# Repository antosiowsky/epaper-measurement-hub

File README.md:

# Epaper-EnvMonitor

A low-power environmental monitoring hub with an e-paper display, based on the M5StampS3 processor. It features a BME688 sensor for temperature, humidity, and air quality measurement, along with data storage and wireless communication.

## Features
- **Real-time environmental monitoring** (temperature, humidity, air quality)
- **E-paper display** for low-power data visualization
- **Data storage** for historical measurements
- **Wireless communication** (Wi-Fi/Bluetooth) for remote access
- **Energy-efficient design** suitable for battery-powered operation

## Hardware Components
- **M5StampS3** – ESP32-S3 based microcontroller
- **BME688** – Temperature, humidity, and gas sensor
- **E-paper display** – Low-power screen for data visualization
- **Memory module** – For data logging and storage

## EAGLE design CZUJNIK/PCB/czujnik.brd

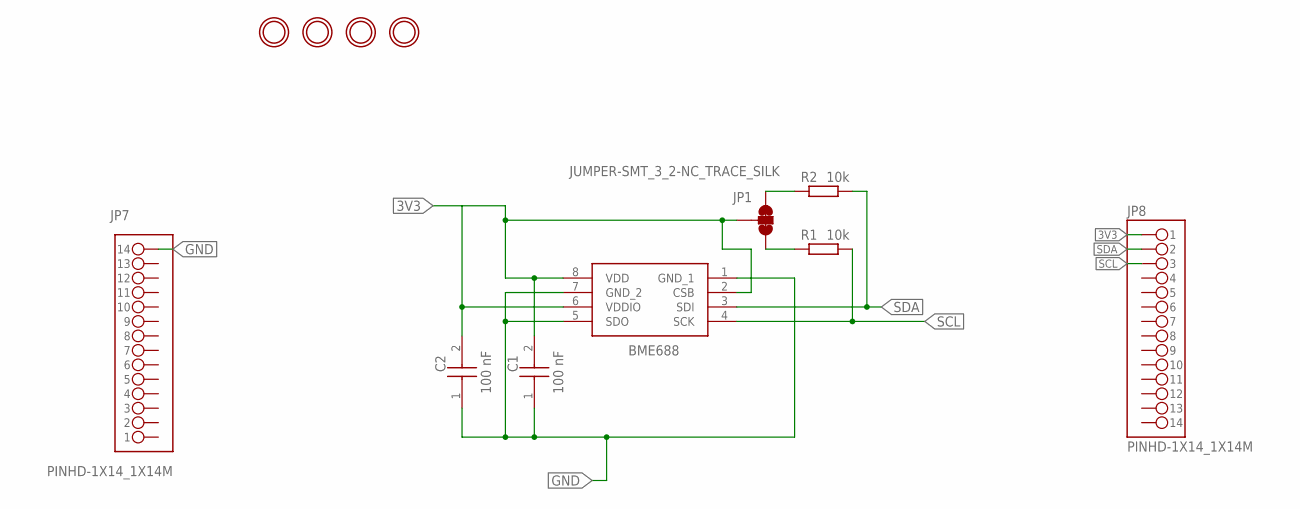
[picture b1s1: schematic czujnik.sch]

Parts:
BME688: BME688
C1, C2: C0603X104K1RACTU; CAPC1608X100N
JP1: JUMPER-SMT_3_2-NC_TRACE_SILK; SMT-JUMPER_3_2-NC_TRACE_SILK
JP7, JP8: PINHD-1X14_1X14M; 1X14
R1, R2: 10k; RESC1005X40
U$2, U$3, U$4, U$6: MOUNTINGHOLE2.5; MOUNTINGHOLE_2.5_PLATED

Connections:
3V3: BME688.2 (CSB), BME688.6 (VDDIO), BME688.8 (VDD), C1.2, C2.2, JP1.2, JP8.1
GND: BME688.1 (GND_1), BME688.5 (SDO), BME688.7 (GND_2), C1.1, C2.1, JP7.14
unnamed: JP1.1, R2.1
unnamed: JP1.3, R1.1
SCL: BME688.4 (SCK), JP8.3, R1.2
SDA: BME688.3 (SDI), JP8.2, R2.2

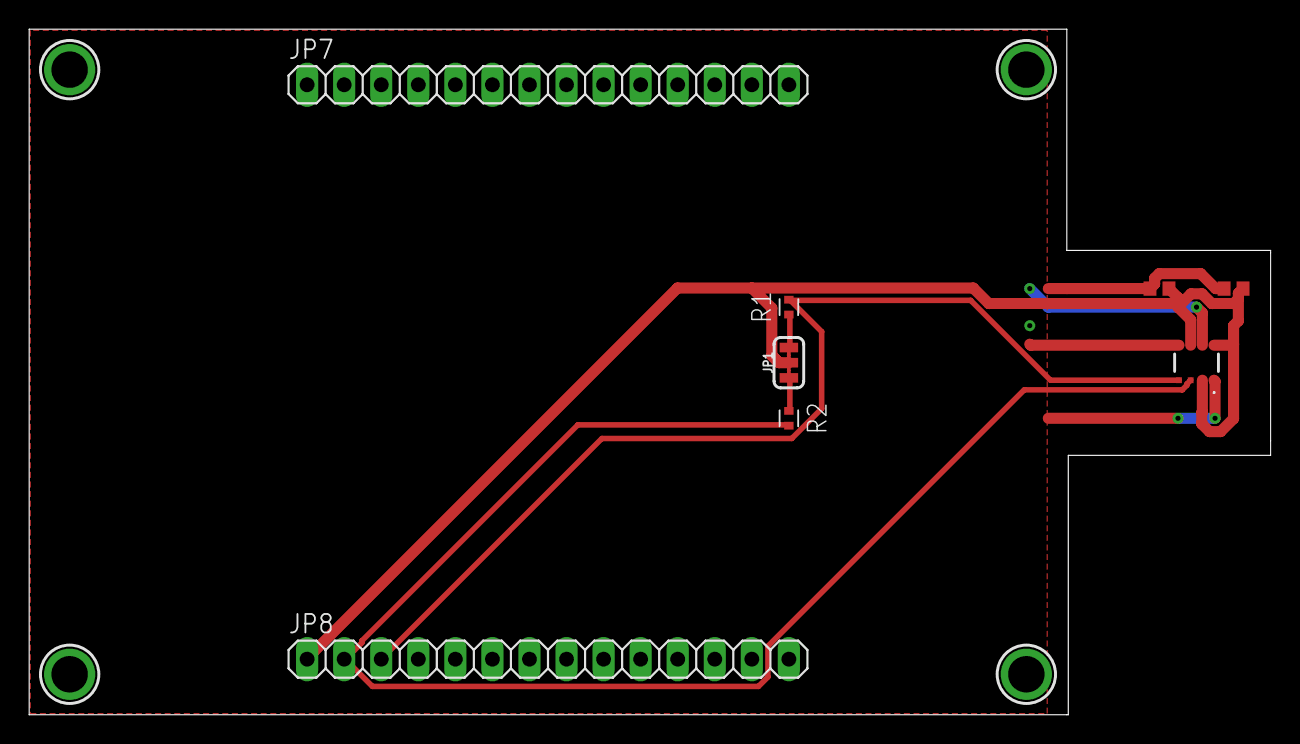
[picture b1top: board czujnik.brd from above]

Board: 2 copper layers, 85.1 x 47.0 mm, 12 parts (0 on the bottom side), 6 nets.

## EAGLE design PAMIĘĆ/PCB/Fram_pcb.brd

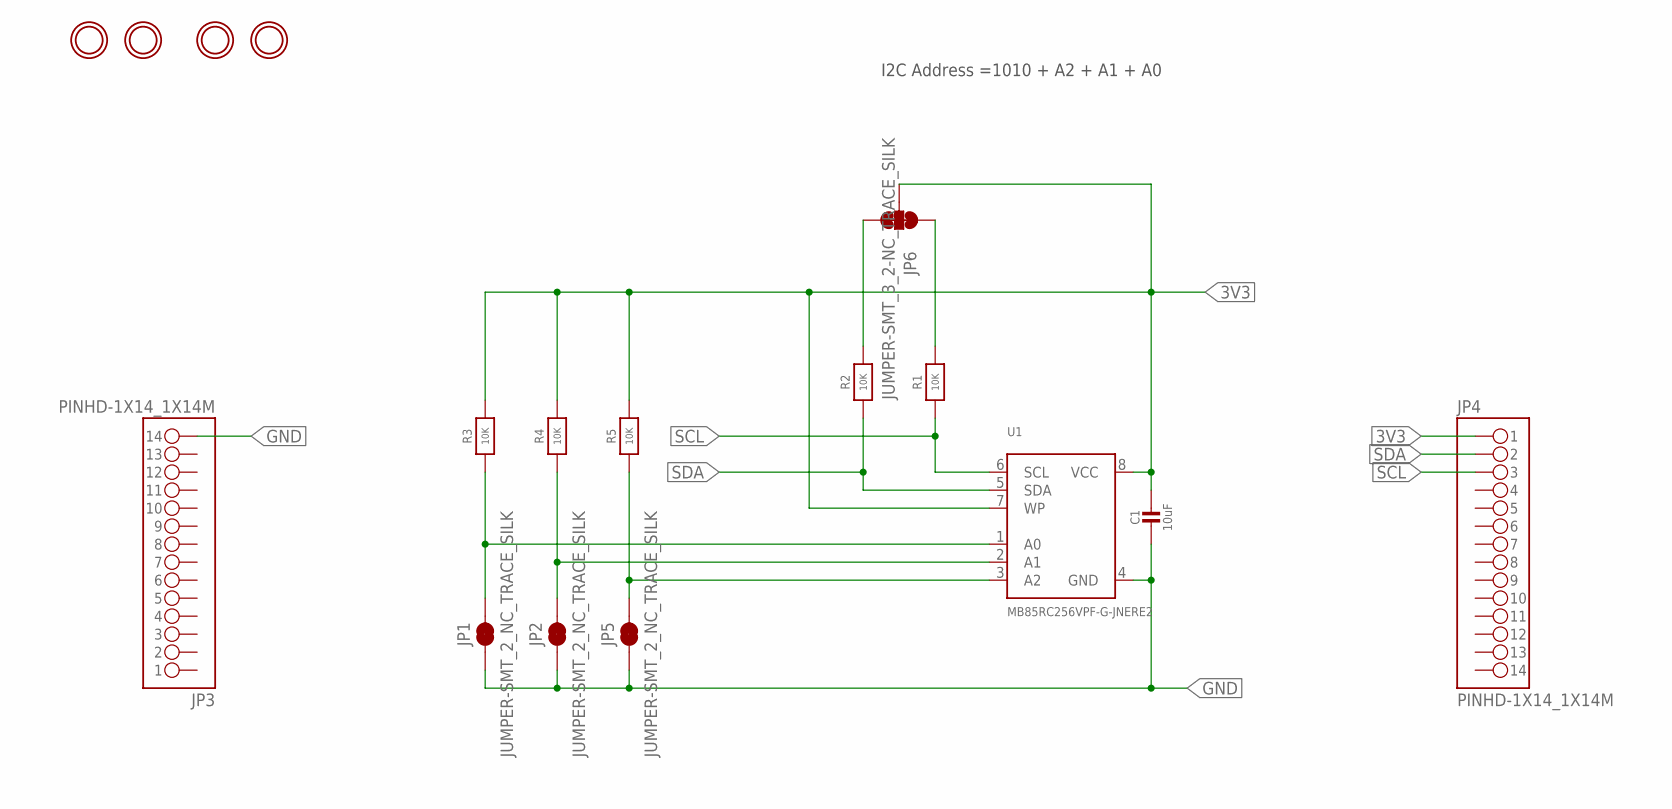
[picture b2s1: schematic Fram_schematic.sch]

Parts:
C1: 10uF; _0805MP
JP1, JP2, JP5: JUMPER-SMT_2_NC_TRACE_SILK; SMT-JUMPER_2_NC_TRACE_SILK
JP3, JP4: PINHD-1X14_1X14M; 1X14
JP6: JUMPER-SMT_3_2-NC_TRACE_SILK; SMT-JUMPER_3_2-NC_TRACE_SILK
R1, R2, R3, R4, R5: 10K; _0805MP
U1: MB85RC256VPF-G-JNERE2; SOIC8_208MIL
U$2, U$3, U$5, U$6: MOUNTINGHOLE2.5; MOUNTINGHOLE_2.5_PLATED

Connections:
3V3: C1.1, JP4.1, JP6.2, R3.2, R4.2, R5.2, U1.7 (WP), U1.8 (VCC)
GND: C1.2, JP1.1, JP2.1, JP3.14, JP5.1, U1.4 (GND)
SCL: JP4.3, JP6.1, R1.1, R1.2, U1.6 (SCL)
SDA: JP4.2, JP6.3, R2.1, R2.2, U1.5 (SDA)
SDA1: JP1.2, R3.1, U1.1 (A0)
SDA2: JP2.2, R4.1, U1.2 (A1)
SDA3: JP5.2, R5.1, U1.3 (A2)

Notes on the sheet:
I2C Address =1010 + A2 + A1 + A0

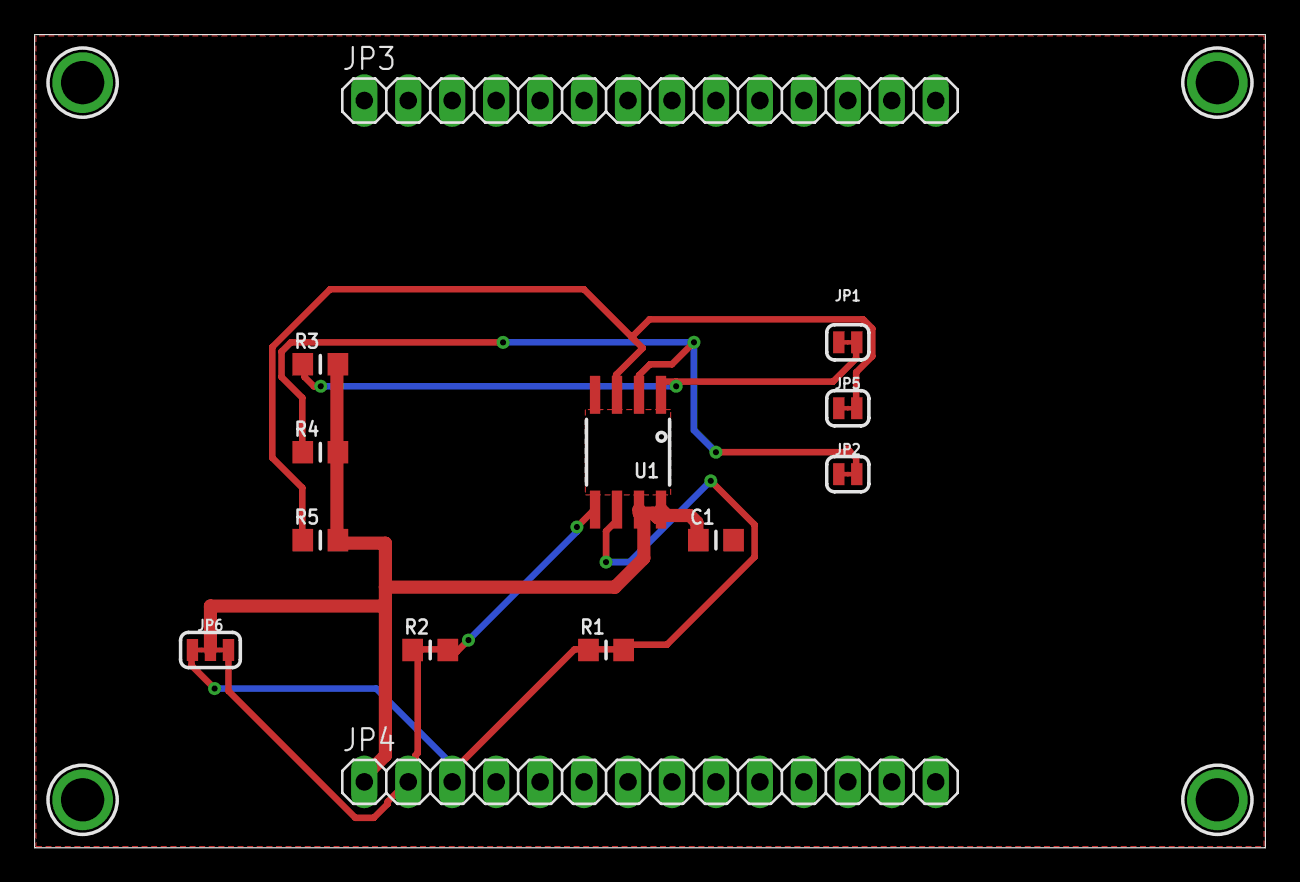
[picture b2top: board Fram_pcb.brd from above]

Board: 2 copper layers, 71.1 x 47.0 mm, 17 parts (0 on the bottom side), 7 nets.

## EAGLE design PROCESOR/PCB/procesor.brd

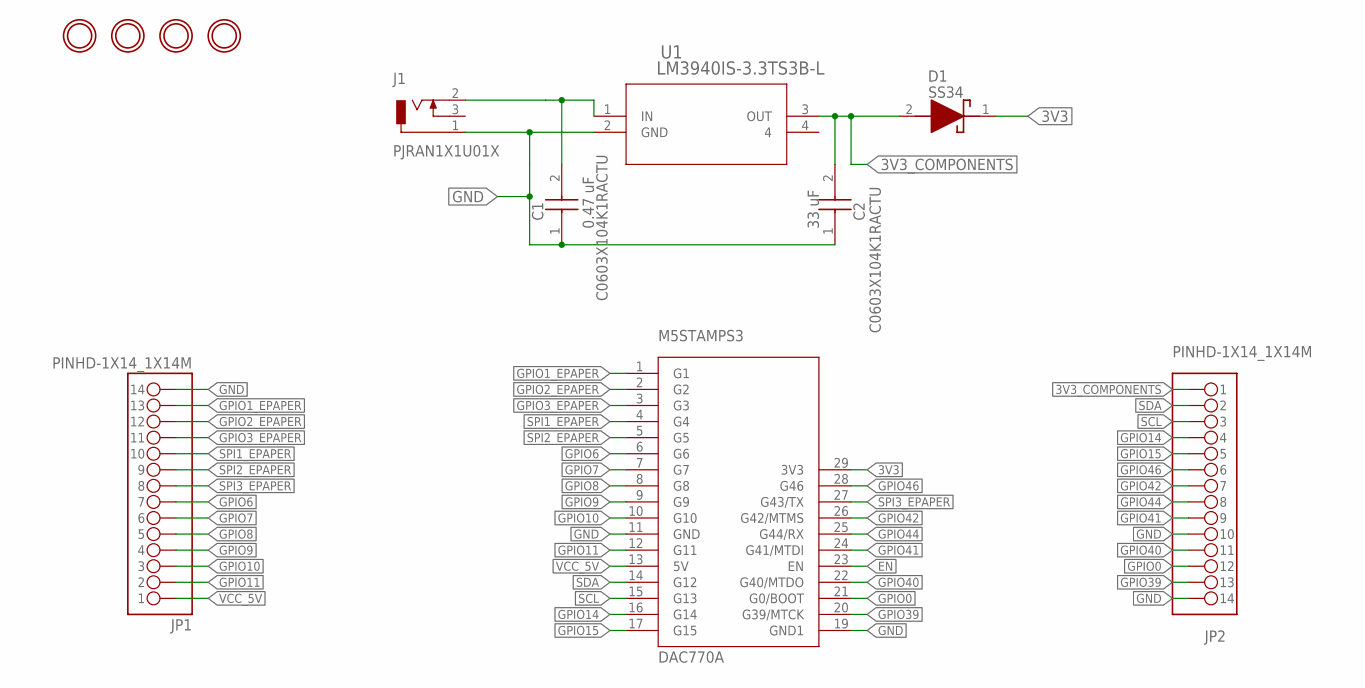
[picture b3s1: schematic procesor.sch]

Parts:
C1, C2: C0603X104K1RACTU; CAPC1608X100N
D1: SS34; DIOM8059X256N
J1: PJRAN1X1U01X
JP1, JP2: PINHD-1X14_1X14M; 1X14
M5STAMPS3: DAC770A; QFN127P2400X1800X470-36N
U1: LM3940IS-3.3TS3B-L; TS3B-L
U$1, U$3, U$5, U$6: MOUNTINGHOLE2.5; MOUNTINGHOLE_2.5_PLATED

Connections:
3V3: D1.1 (K), M5STAMPS3.29 (3V3)
3V3_COMPONENTS: C2.2, D1.2 (A), JP2.1, U1.3 (OUT)
EN: M5STAMPS3.23 (EN)
GND: C1.1, C2.1, J1.1, JP1.14, JP2.10, JP2.14, M5STAMPS3.11 (GND), M5STAMPS3.19 (GND1), U1.2 (GND)
GPIO0: JP2.12, M5STAMPS3.21 (G0/BOOT)
GPIO1_EPAPER: JP1.13, M5STAMPS3.1 (G1)
GPIO2_EPAPER: JP1.12, M5STAMPS3.2 (G2)
GPIO3_EPAPER: JP1.11, M5STAMPS3.3 (G3)
GPIO6: JP1.7, M5STAMPS3.6 (G6)
GPIO7: JP1.6, M5STAMPS3.7 (G7)
GPIO8: JP1.5, M5STAMPS3.8 (G8)
GPIO9: JP1.4, M5STAMPS3.9 (G9)
GPIO10: JP1.3, M5STAMPS3.10 (G10)
GPIO11: JP1.2, M5STAMPS3.12 (G11)
GPIO14: JP2.4, M5STAMPS3.16 (G14)
GPIO15: JP2.5, M5STAMPS3.17 (G15)
GPIO39: JP2.13, M5STAMPS3.20 (G39/MTCK)
GPIO40: JP2.11, M5STAMPS3.22 (G40/MTDO)
GPIO41: JP2.9, M5STAMPS3.24 (G41/MTDI)
GPIO42: JP2.7, M5STAMPS3.26 (G42/MTMS)
GPIO44: JP2.8, M5STAMPS3.25 (G44/RX)
GPIO46: JP2.6, M5STAMPS3.28 (G46)
unnamed: C1.2, J1.2, U1.1 (IN)
SCL: JP2.3, M5STAMPS3.15 (G13)
SDA: JP2.2, M5STAMPS3.14 (G12)
SPI1_EPAPER: JP1.10, M5STAMPS3.4 (G4)
SPI2_EPAPER: JP1.9, M5STAMPS3.5 (G5)
SPI3_EPAPER: JP1.8, M5STAMPS3.27 (G43/TX)
VCC_5V: JP1.1, M5STAMPS3.13 (5V)

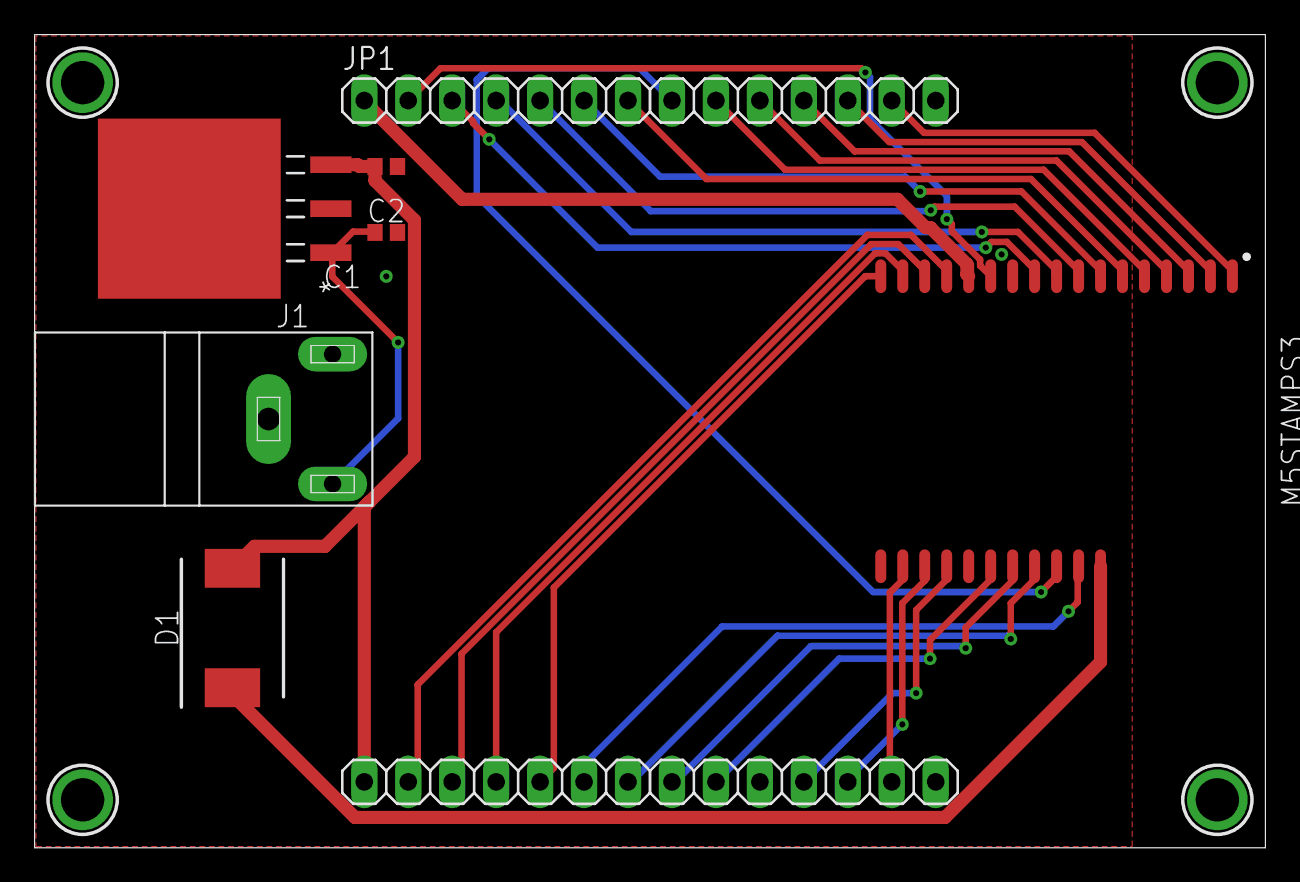
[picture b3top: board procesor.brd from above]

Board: 2 copper layers, 71.1 x 46.9 mm, 12 parts (0 on the bottom side), 28 nets.

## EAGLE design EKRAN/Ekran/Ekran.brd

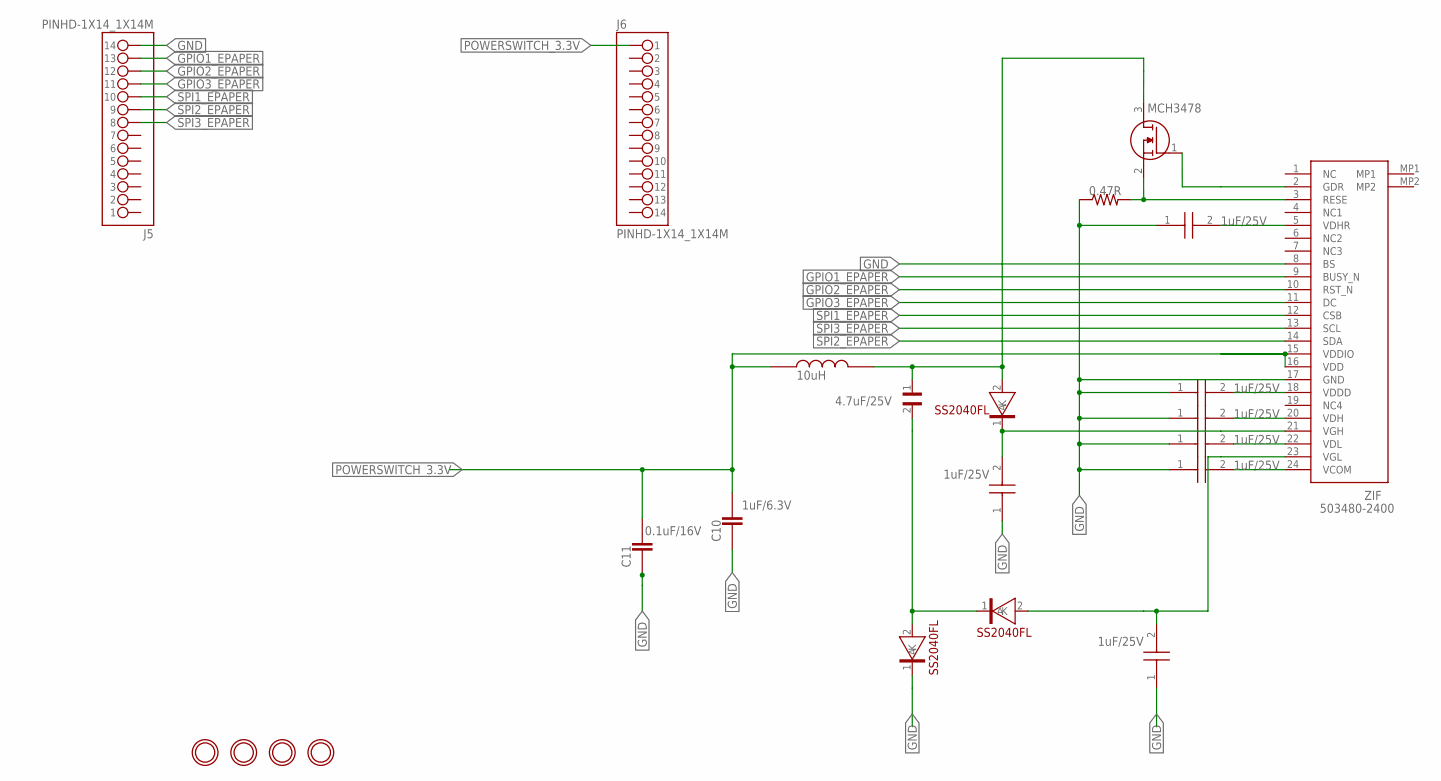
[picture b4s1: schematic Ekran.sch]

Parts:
C1, C2, C3, C4, C5, C6, C8: MAJCT168BB7105KTEA01; MAJX16
C7: 4.7uF/25V; CAPC3225X280N
C10: 1uF/6.3V; CAPC1608X90
C11: 0.1uF/16V; CAPC1608X90
J5, J6: PINHD-1X14_1X14M; 1X14
L2: 10uH; INDC1608X95N
Q1: MCH3478; SOTFL65P210X90-3N
R1: 0.47R; RESAD724W46L381D178B
U$1, U$2, U$3: SS2040FL; SOD-123FL
U$4, U$5, U$6, U$7: MOUNTINGHOLE2.5; MOUNTINGHOLE_2.5_PLATED
ZIF: 503480-2400; 5034802400

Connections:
GND: C1.1, C2.1, C3.1, C4.1, C5.1, C6.1, C8.1, C10.1, C11.1, J5.14, R1.1, U$2.1 (K), ZIF.8 (BS), ZIF.17 (GND)
GPIO1_EPAPER: J5.13, ZIF.9 (BUSY_N)
GPIO2_EPAPER: J5.12, ZIF.10 (RST_N)
GPIO3_EPAPER: J5.11, ZIF.11 (DC)
unnamed: Q1.1 (G), ZIF.2 (GDR)
unnamed: C5.2, ZIF.5 (VDHR)
unnamed: C4.2, ZIF.18 (VDDD)
unnamed: C7.2, U$2.2 (A), U$3.1 (K)
unnamed: C7.1, L2.2, Q1.3 (D), U$1.2 (A)
unnamed: C1.2, ZIF.20 (VDH)
unnamed: C6.2, U$1.1 (K), ZIF.21 (VGH)
unnamed: C2.2, ZIF.22 (VDL)
unnamed: C8.2, U$3.2 (A), ZIF.23 (VGL)
unnamed: C3.2, ZIF.24 (VCOM)
unnamed: Q1.2 (S), R1.2, ZIF.3 (RESE)
POWERSWITCH_3.3V: C10.2, C11.2, J6.1, L2.1, ZIF.15 (VDDIO), ZIF.16 (VDD)
SPI1_EPAPER: J5.10, ZIF.12 (CSB)
SPI2_EPAPER: J5.9, ZIF.14 (SDA)
SPI3_EPAPER: J5.8, ZIF.13 (SCL)

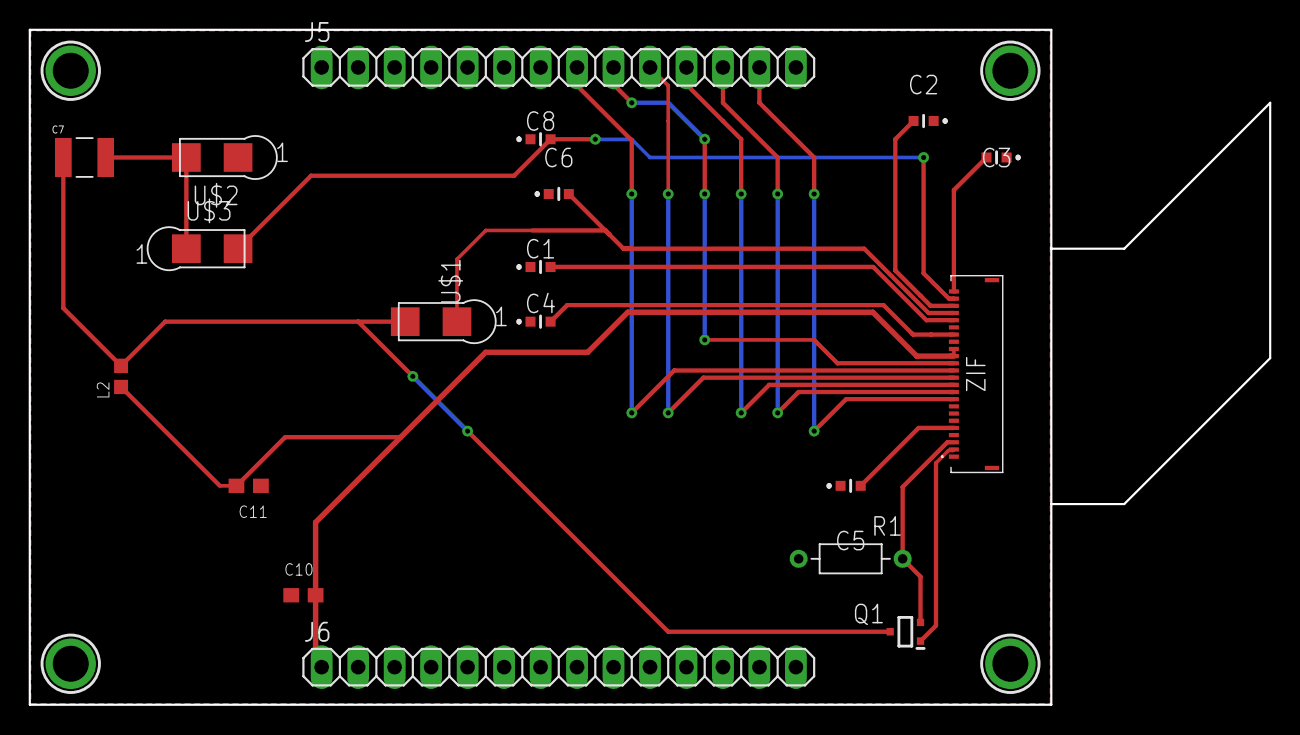
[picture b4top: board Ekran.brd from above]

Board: 2 copper layers, 86.4 x 47.0 mm, 23 parts (0 on the bottom side), 19 nets.

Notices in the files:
parts and their libraries:
microbuilder: This work is placed in the public domain, and may be freely used for commercial and non-commercial work with the following conditions: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
SparkFun-Jumpers: Licensing: Creative Commons ShareAlike 4.0 International - https://creativecommons.org/licenses/by-sa/4.0
